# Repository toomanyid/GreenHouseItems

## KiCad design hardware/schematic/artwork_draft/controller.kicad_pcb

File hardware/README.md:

# 측창 모터 제어기 하드웨어

프로젝트 공유 폴더의 회로도 작업을 그대로 옮겨 둔 것이다.

- `schematic/` 제어 기판 회로도(빵판 기준 통합본, 손 납땜 PCB)
  - `제어기_회로도.svg/.png`, `제어기_부품배치도.svg/.png`
  - `제어기_아트웍_의뢰.pdf` 아트웍 의뢰서 (`controller_artwork_request.pdf`는 같은 파일의 영문 이름)
  - `artwork_draft/` KiCad PCB 초안, 거버 초안, 확인용 PDF
  - `src/` 위 결과물을 만드는 파이썬 원본 (`schematic.py` 회로도, `bom.py` 부품표, `pcb_*.py` PCB, `make_pdf.py`와 `pdf.js` 의뢰서 PDF)
- `changes/` 회로 변경안 메모 (확인받아 반영한 내용)
- `old/` 통합 전의 빵판 회로도와 베이스 보드 회로도. 지금은 `schematic/`이 기준이다.

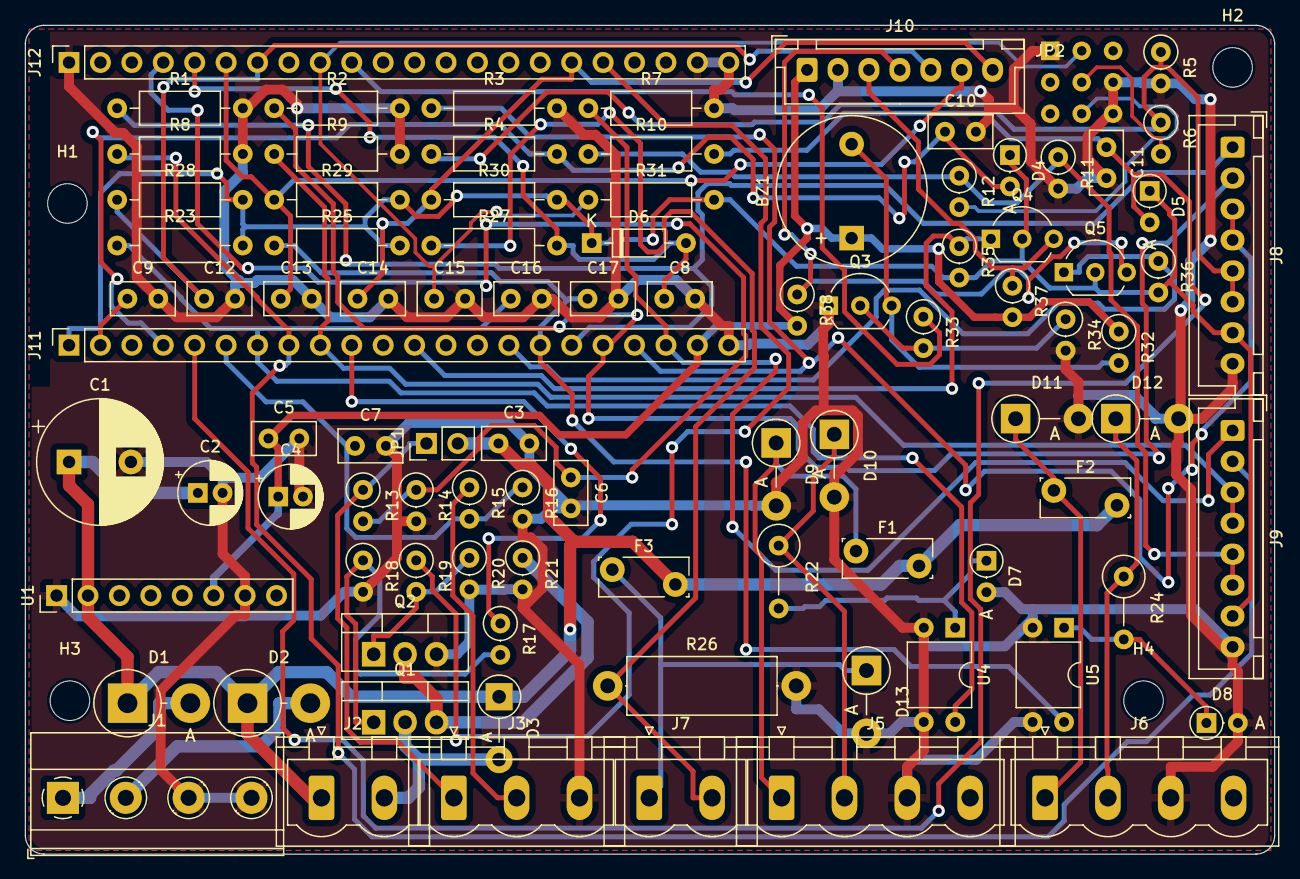
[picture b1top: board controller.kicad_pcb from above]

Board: 2 copper layers, 101.0 x 67.0 mm, 97 parts (0 on the bottom side), 50 nets.

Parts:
BZ1: Buzzer_12x9.5RM7; Buzzer_12x9.5RM7.6
C1: 470uF; CP_Radial_D10.0mm_P5.00mm
C2, C4: 22uF; CP_Radial_D5.0mm_P2.00mm
C3, C5, C6, C7, C8, C9: 100nF; C_Disc_D5.0mm_W2.5mm_P2.50mm
C10, C11: 1uF; C_Disc_D5.0mm_W2.5mm_P2.50mm
C12, C13, C14, C15, C16, C17: 10nF; C_Disc_D5.0mm_W2.5mm_P2.50mm
D1, D2: 1N5822; D_DO-201AD_P5.08mm_Vertical_AnodeUp
D3: 1N4007; D_DO-41_SOD81_P5.08mm_Vertical_AnodeUp
D4, D5: BAT85; D_DO-35_SOD27_P2.54mm_Vertical_AnodeUp
D6: BAT85; D_DO-35_SOD27_P7.62mm_Horizontal
D7, D8: 1N4148; D_DO-35_SOD27_P2.54mm_Vertical_AnodeUp
D9, D10, D11, D12, D13: P6KE30A; D_DO-15_P5.08mm_Vertical_AnodeUp
F1, F2, F3: PTC; Fuse_Bourns_MF-RG300
H1, H2, H3, H4: MountingHole_3.2; MountingHole_3.2mm_M3
J1: 24V_A; TerminalBlock_Phoenix_MKDS-1,5-4-5.08_1x04_P5.08mm_Horizont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
J2: MC; PhoenixContact_MSTBVA_2,5_2-G-5,08_1x02_P5.08mm_Vertical
J3: ESTOP; PhoenixContact_MSTBVA_2,5_3-G-5,08_1x03_P5.08mm_Vertical
J5, J6: PhoenixContact_M; PhoenixContact_MSTBVA_2,5_4-G-5,08_1x04_P5.08mm_Vertical
J7: PhoenixContact_M; PhoenixContact_MSTBVA_2,5_2-G-5,08_1x02_P5.08mm_Vertical
J8, J9: XH; JST_XH_B8B-XH-A_1x08_P2.50mm_Vertical
J10: XH; JST_XH_B7B-XH-A_1x07_P2.50mm_Vertical
J11, J12: ESP32; PinSocket_1x22_P2.54mm_Vertical
JP1: 50W; PinHeader_1x02_P2.54mm_Vertical
JP2: PinHeader_3x03_P; PinHeader_3x03_P2.54mm
Q1, Q2: IRLZ44N; TO-220-3_Vertical
Q3, Q4, Q5: 2N7000; TO-92_Inline_Wide
R1, R2, R3, R4, R7, R8, R9, R10, R23, R25, R27, R28, R29, R30, R31: 10k; R_Axial_DIN0207_L6.3mm_D2.5mm_P10.16mm_Horizontal
R5, R11: 2.2k; R_Axial_DIN0207_L6.3mm_D2.5mm_P2.54mm_Vertical
R6, R12: 1.3k; R_Axial_DIN0207_L6.3mm_D2.5mm_P2.54mm_Vertical
R13, R15, R21: 100k; R_Axial_DIN0207_L6.3mm_D2.5mm_P2.54mm_Vertical
R14, R16, R18, R20, R34: 10k; R_Axial_DIN0207_L6.3mm_D2.5mm_P2.54mm_Vertical
R17, R19, R33: 100R; R_Axial_DIN0207_L6.3mm_D2.5mm_P2.54mm_Vertical
R22, R24: 2.2k; R_Axial_DIN0309_L9.0mm_D3.2mm_P5.08mm_Vertical
R26: 120R; R_Axial_DIN0414_L11.9mm_D4.5mm_P15.24mm_Horizontal
R32: 1k; R_Axial_DIN0207_L6.3mm_D2.5mm_P2.54mm_Vertical
R35, R36, R37, R38: 4.7k; R_Axial_DIN0207_L6.3mm_D2.5mm_P2.54mm_Vertical
U1: URB4805S; PinHeader_1x08_P2.54mm_Vertical
U4, U5: PC817; DIP-4_W7.62mm

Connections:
24V_A: D1.2, J1.1
24V_B: D2.2, J1.2
24V_F: C1.1, C2.1, C3.1, D1.1, D2.1, D3.1, F1.2, F2.2, F3.2, J2.1, JP1.2, U1.2
+3V3: C9.1, D4.1, D5.1, D6.1, J8.7, J9.7, J11.1, J11.2, Q4.2, Q5.2, R23.2, R25.2, R28.2, R29.2, R30.2, R31.2, R35.2, R36.2
+5V: BZ1.1, C4.1, C5.1, J10.1, J11.21, R32.1, R37.2, R38.2, U1.6
BZ_D: BZ1.2, Q3.3, R32.2
COIL-: D3.2, J2.2, Q1.2
ESTOP_IN: J3.1, JP1.1, R13.1
GND: C1.2, C2.2, C3.2, C4.2, C5.2, C6.2, C7.2, C8.2, C9.2, C10.2, C11.2, C12.2, C13.2, C14.2, C15.2, C16.2, C17.2, D7.2, D8.2, D9.2, D10.2, D11.2, D12.2, D13.2, J1.3, J1.4, J3.3, J5.3, J6.3, J8.8, J9.8, J10.2, J11.22, J12.1, J12.21, J12.22, JP2.1, JP2.6, JP2.9, Q2.3, Q3.1, R1.2, R2.2, R3.2, R5.2, R7.2, R8.2, R9.2, R11.2, R14.2, R16.2, R18.2, R20.2, R21.2, R26.2, R34.2, U1.1, U1.7, U4.2, U4.3, U5.2, U5.3
IO1: C6.1, J12.4, R13.2, R14.1
IO2: C8.1, D6.2, J12.5, R27.2
IO4: C10.1, D4.2, J11.4, R4.2
IO5: C11.1, D5.2, J11.5, R10.2
IO6: C7.1, J11.6, R15.2, R16.1
IO7: C16.1, J11.7, R23.1, U4.4
IO8: J11.12, Q4.1, R35.1
IO9: J11.15, Q5.1, R36.1
IO10: C17.1, J11.16, R25.1, U5.4
IO11: J8.1, J11.17, R1.1
IO12: J8.2, J11.18, R2.1
IO13: J8.3, J8.4, J11.19, R3.1
IO14: J9.1, J11.20, R7.1
IO15: J9.2, J11.8, R8.1
IO16: J9.3, J9.4, J11.9, R9.1
IO17: J11.10, R17.1
IO21: J12.18, R19.1
IO38: J12.10, R33.1
IO39: C15.1, J12.9, JP2.2, R31.1
IO41: C12.1, J10.5, J12.7, R28.1
IO42: C13.1, J10.6, J12.6, R29.1
IO47: C14.1, J10.7, J12.17, R30.1
M1_ISN: J8.5, J8.6, R4.1, R5.1, R6.1
M1_SEL: JP2.5, R6.2
M2_ISN: J9.5, J9.6, R10.1, R11.1, R12.1
M2_SEL: JP2.8, R12.2
Q1_G: Q1.1, R17.2, R18.1
Q2_G: Q2.1, R19.2, R20.1
Q3_G: Q3.2, R33.2, R34.1
Q_MID: Q1.3, Q2.2, R21.1
RLY_OUT: J3.2, R15.1
S1_LED: D7.1, R22.2, U4.1
S1_P24: D9.1, F1.1, J5.1
S1_SIG: D10.1, J5.2, R22.1
S2_LED: D8.1, R24.2, U5.1
S2_P24: D11.1, F2.1, J6.1
S2_SIG: D12.1, J6.2, R24.1
SCL_5V: J10.4, Q5.3, R38.1
SDA_5V: J10.3, Q4.3, R37.1
T_M: J7.2, R26.1, R27.1
T_P: D13.1, F3.1, J7.1

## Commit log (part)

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2026-01-31 main
2026-01-31 test
2026-02-01 싱글톤으로 수정. state 패턴 적용. 설정값 저장/로드 기능 추가
2026-02-01 아직은 기본 구성중.
2026-02-01 아이들과 런을 구성하고 있는중.
2026-02-01 설정 화면 구성중.
2026-02-03 화면 표시를 시간에서 퍼센트로 변경 top이상으로 이동 할 수 없도록 수정. up, down 버튼을 누르면 다음 목표로 이동.
2026-02-03 설정에 최대전류값을 추가.
2026-02-03 전류 에따른 모터 정지 기능 추가.
2026-02-03 화면 표시를 퍼센트로 변경시
2026-02-10 모터 현제위치 표시 방법 변경
2026-02-21 모터 드라이버에서 과전류 콜백 직접 받음.
2026-02-21 min, zero, limit, max 로 모터 위치명 수정.
2026-02-21 키큐를 이용하는 방법으로 키 입력방법 수정.
2026-02-21 키입력시 눌릴때만 입력으로 확인 하도록 수정.
2026-02-25 버튼입력이 놓을때도 입력되는문제 수정.
2026-03-06 설정을 min, bottom, top, max 로 변경.
2026-03-06 실수형에서 10배수 정수형으로 변경.
2026-03-06 전류도 10배수 정수로 관리.
2026-03-06 컴파일 문제 수정.
2026-03-06 아이들에서 로터리 회전시 1초씩 증감.
2026-04-12 PicoMotorController: nine-grid RUN OLED layout, 2s encoder arm delay
2026-04-13 PicoMotorController: 2s soft start, speed-aware position, HB current
2026-04-13 PicoMotorController: stop RUN on encoder push (debounced)
2026-05-16 PicoMotorController: enter SETUP on 5s PSH hold, recalibrate I-zero
2026-05-16 Add MotorController2: Modbus RTU motor control with OLED and flash settings
2026-05-16 ssh 초기화
2026-05-21 모터 콘트롤러2 추가.
